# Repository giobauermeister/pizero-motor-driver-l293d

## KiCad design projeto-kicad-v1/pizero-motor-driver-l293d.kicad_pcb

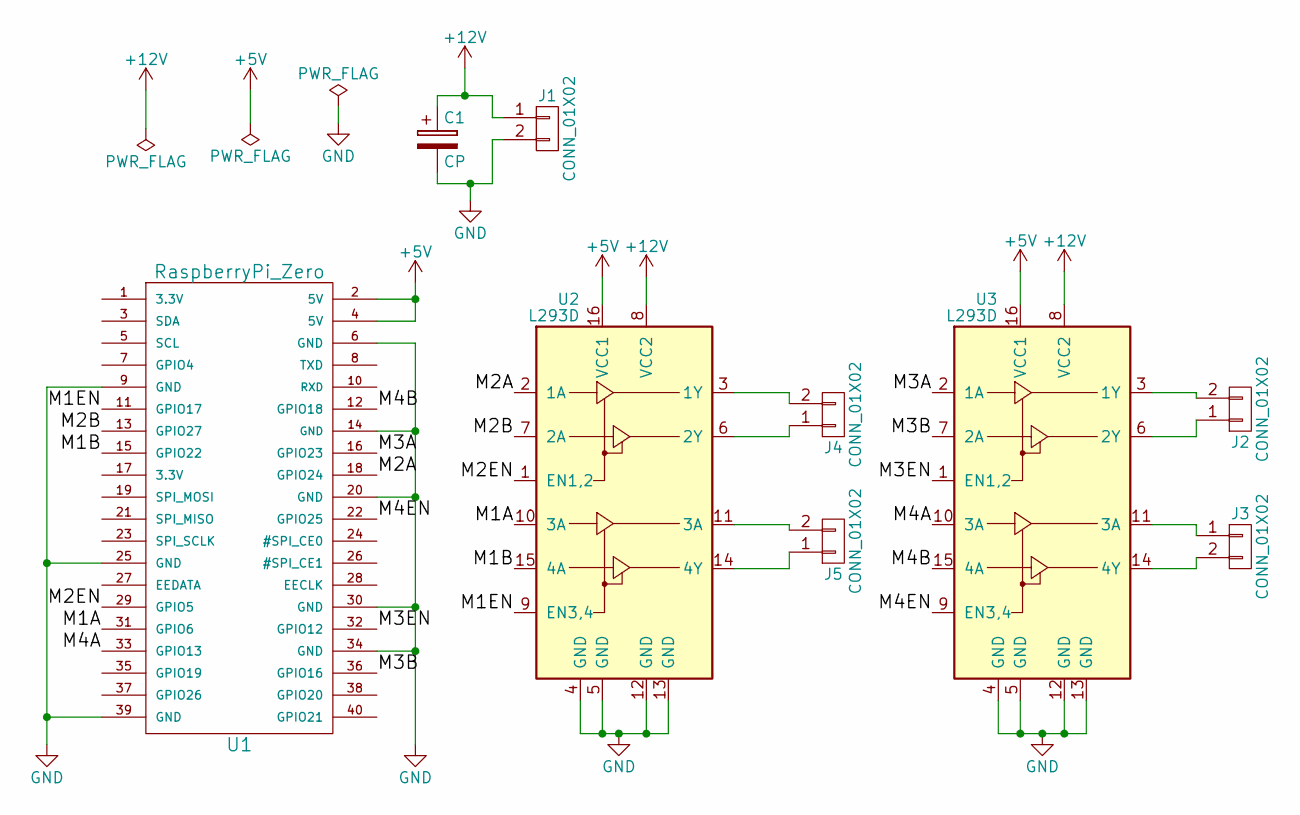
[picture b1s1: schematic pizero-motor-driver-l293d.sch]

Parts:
C1: CP; CP_Radial_D5.0mm_P2.50mm
J1, J2, J3, J4, J5: CONN_01X02; KRE_5.0mm_2pins
U1: RaspberryPi_Zero; RaspberryPi_Hat_no_holes
U2, U3: L293D; DIP-16_W7.62mm

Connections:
+5V: U1.2 (5V), U1.4 (5V), U2.16 (VCC1), U3.16 (VCC1)
+12V: C1.1, J1.1, U2.8 (VCC2), U3.8 (VCC2)
/M1A: U1.31 (GPIO6), U2.10 (3A)
/M1B: U1.15 (GPIO22), U2.15 (4A)
/M1EN: U1.11 (GPIO17), U2.9 (EN3,4)
/M2A: U1.18 (GPIO24), U2.2 (1A)
/M2B: U1.13 (GPIO27), U2.7 (2A)
/M2EN: U1.29 (GPIO5), U2.1 (EN1,2)
/M3A: U1.16 (GPIO23), U3.2 (1A)
/M3B: U1.36 (GPIO16), U3.7 (2A)
/M3EN: U1.32 (GPIO12), U3.1 (EN1,2)
/M4A: U1.33 (GPIO13), U3.10 (3A)
/M4B: U1.12 (GPIO18), U3.15 (4A)
/M4EN: U1.22 (GPIO25), U3.9 (EN3,4)
GND: C1.2, J1.2, U1.6 (GND), U1.9 (GND), U1.14 (GND), U1.20 (GND), U1.25 (GND), U1.30 (GND), U1.34 (GND), U1.39 (GND), U2.4 (GND), U2.5 (GND), U2.12 (GND), U2.13 (GND), U3.4 (GND), U3.5 (GND), U3.12 (GND), U3.13 (GND)
unnamed: J2.1, U3.6 (2Y)
unnamed: J2.2, U3.3 (1Y)
unnamed: J3.1, U3.11 (3A)
unnamed: J3.2, U3.14 (4Y)
unnamed: J4.1, U2.6 (2Y)
unnamed: J4.2, U2.3 (1Y)
unnamed: J5.1, U2.14 (4Y)
unnamed: J5.2, U2.11 (3A)

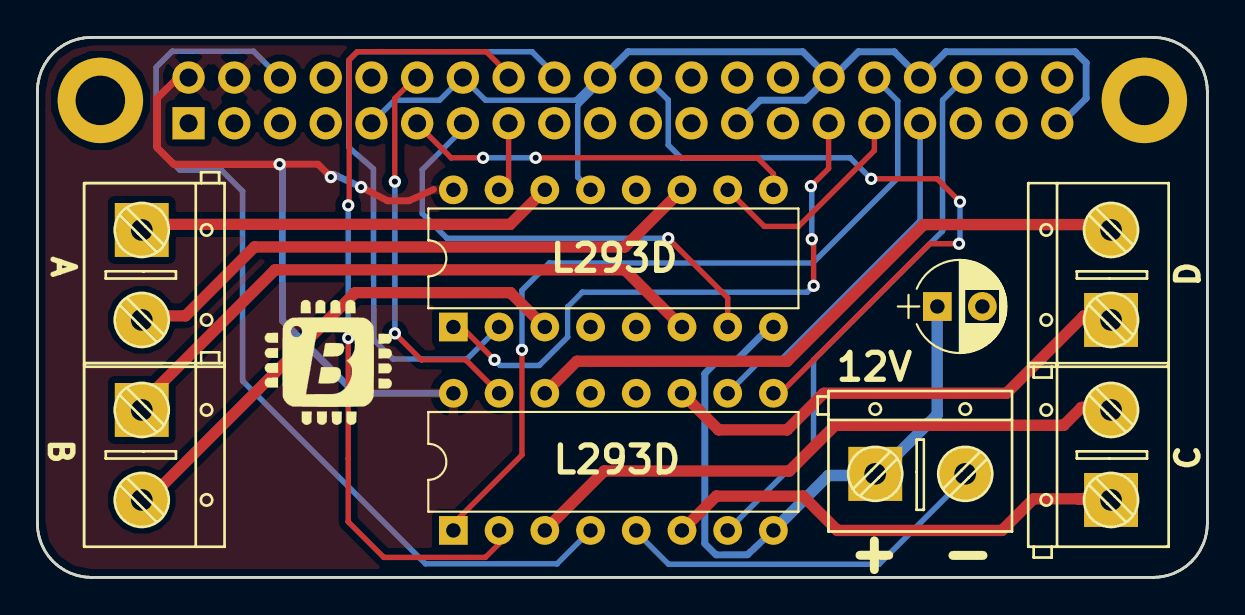
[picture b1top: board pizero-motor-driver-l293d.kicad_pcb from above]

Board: 2 copper layers, 65.0 x 30.0 mm, 9 parts (0 on the bottom side), 23 nets.

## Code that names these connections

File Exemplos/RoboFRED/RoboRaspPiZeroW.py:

from time import sleep
import RPi.GPIO as GPIO
import paho.mqtt.client as mqtt
import sys

#variaveis globais
Broker = "iot.eclipse.org"
PortaBroker = 1883
KeepAliveBroker = 60
TopicoSubscribe = "RaspZeroWRobo"  #No formato: "mcs/deviceId/deviceKey/dataChnId", onde dataChnId e referente ao data channel Controller

# definicao dos pinos
M1A = 31
M1B = 15
M1EN = 11
M2A = 18 
M2B = 13
M2EN = 29 

#Callback - conexao ao broker realizada
def on_connect(client, userdata, flags, rc):
    print("[STATUS] Conectado ao Broker.")
 
    #faz subscribe automatico no topico
    client.subscribe(TopicoSubscribe,0)
 
#Callback - mensagem recebida do broker
def on_message(client, userdata, msg):
 MensagemRecebida = str(msg.payload)
 print("[MSG RECEBIDA] Topico: "+msg.topic+" / Mensagem: "+MensagemRecebida)
 
 #verifica qual a movimentacao desejada
 #Frente (os dois motores no sentido horario):
 if (MensagemRecebida == "F"):
	GPIO.output(M1EN, GPIO.HIGH)
	GPIO.output(M2EN, GPIO.HIGH)
	GPIO.output(M1A, GPIO.HIGH)
	GPIO.output(M1B, GPIO.LOW)
	GPIO.output(M2A, GPIO.HIGH)
	GPIO.output(M2B, GPIO.LOW)
	return
 
 #Esquerda (Motor 1 no sentido horario e Motor 2 no sentido anti-horario):
 if (MensagemRecebida == "E"):
	GPIO.output(M1EN, GPIO.HIGH)
	GPIO.output(M2EN, GPIO.HIGH)
	GPIO.output(M1A, GPIO.HIGH)
	GPIO.output(M1B, GPIO.LOW)
	GPIO.output(M2A, GPIO.LOW)
	GPIO.output(M2B, GPIO.HIGH)
	return
 
 #Direita (Motor 2 no sentido horario e Motor 1 no sentido anti-horario):
 if (MensagemRecebida == "D"):
	GPIO.output(M1EN, GPIO.HIGH)
	GPIO.output(M2EN, GPIO.HIGH)
	GPIO.output(M1A, GPIO.LOW)
	GPIO.output(M1B, GPIO.HIGH)
	GPIO.output(M2A, GPIO.HIGH)
	GPIO.output(M2B, GPIO.LOW)
	return

 #Re (Motor 1 e 2 no sentido anti-horario):
 if (MensagemRecebida == "R"):
	GPIO.output(M1EN, GPIO.HIGH)
	GPIO.output(M2EN, GPIO.HIGH)
	GPIO.output(M1A, GPIO.LOW)
	GPIO.output(M1B, GPIO.HIGH)
	GPIO.output(M2A, GPIO.LOW)
	GPIO.output(M2B, GPIO.HIGH)
	return

 #Parado (Motor 1 e 2 parados):
 if (MensagemRecebida == "P"):
	GPIO.output(M1EN, GPIO.LOW)
	GPIO.output(M2EN, GPIO.LOW)
	return

	

#----------------------
#  Programa principal
#----------------------

# inicia a biblioteca RPi.GPIO usando numeracao do Header
GPIO.setwarnings(False)
GPIO.setmode(GPIO.BOARD)

# configura os pinos do driver como saida
GPIO.setup(M1A, GPIO.OUT)
GPIO.setup(M2A, GPIO.OUT)

GPIO.setup(M1B, GPIO.OUT)
GPIO.setup(M2B, GPIO.OUT)

GPIO.setup(M1EN, GPIO.OUT)
GPIO.setup(M2EN, GPIO.OUT)

#inicializa motores como desligados
GPIO.output(M1EN, GPIO.HIGH)
GPIO.output(M2EN, GPIO.HIGH)
GPIO.output(M1A, GPIO.HIGH)
GPIO.output(M1B, GPIO.LOW)
GPIO.output(M1EN, GPIO.LOW)
GPIO.output(M2EN, GPIO.LOW)

try:
	print("[STATUS] Inicializando MQTT...")
 
        #inicializa MQTT:
        client = mqtt.Client()
        client.on_connect = on_connect
        client.on_message = on_message
 
        client.connect(Broker, PortaBroker, KeepAliveBroker)
        client.loop_forever()
except KeyboardInterrupt:
        print "\nCtrl+C pressionado, encerrando aplicacao e saindo..."
        sys.exit(0)

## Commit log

2017-10-02 Create Exemplos
2017-10-02 Create RoboFRED
